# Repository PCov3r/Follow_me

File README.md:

# Follow me

***Follow me*** est un projet de première année d'école d'ingénieur créé par 9 étudiants.<br>
Le but est de suivre une personne grâce à un algorithme de reconnaissance faciale et de faire du streaming. On utilise ainsi une raspberry, une carte STM32 et 2 servo-moteurs (un pour le pan et un pour le tilt).<br> On a également implémenté un contrôle manuel du tracking par le biais d'API coté serveur et d'une autre raspberry et d'une STM32 coté commande.

## Serveur et streaming

[Section relative au serveur flask et au tracking](WebServer/FlaskServer/)

Nous avons utilisé la librairie OpenCV pour faire du tracking et la librairie Flask pour implémenter le serveur web et le streaming.<br>

### Tracking et API

La librairie OpenCV possède de manière native différents trackers, dont les détails peuvent être trouvés [ici](https://learnopencv.com/object-tracking-using-opencv-cpp-python/) et [ici](https://ehsangazar.com/object-tracking-with-opencv-fd18ccdd7369). Dans notre cas, nous utilisons le tracker KCF qui est non seulement précis, mais qui retrouve également la personne si celle-ci sort et rentre dans le champ de la caméra. <br>
Le passage du mode tracking automatique au mode contrôle manuel est assuré par le biais d'[API](https://flask.palletsprojects.com/en/2.0.x/api/) sous forme de requêtes HTTP. Le serveur Flask reçoit ces requêtes, en analyse les arguments, et agit en conséquence.
<br>
### Communication avec la carte STM32

La communication entre la Raspberry Pi et la carte STM32 gérant la caméra et les servo-moteurs se fait via le protocole [UART](https://www.raspberrypi.org/documentation/configuration/uart.md). Des détails sur le protocole mis en place se trouvent dans la section relative au contrôle des servos.
Il est à noter que le contrôle des mouvements est pour le moment très naïf. En effet, on indique simplement à la STM32 dans quelle direction on souhaite orienter la caméra. 
<br>
Nous avons en effet abandonné l'idée d'indiquer précisément à la carte la position relative de l'utilisateur, ceci pour des raisons de simplicité et surtout de temps.
Une source d'amélioration serait ainsi d'implémenter cela et d'agir en conséquence sur la vitesse de déplacement afin de s'assurer de ne jamais perdre l'utilisateur.
<br>
### Liste des packages à installer pour le serveur web et tracking

pip : ``sudo apt-get install python3-pip`` <br>
imutils : ``pip3 install imutils`` <br>
opencv : ``apt-get install python3-opencv``<br>
flask : ``pip3 install flask``

<br>
<br>

## Contrôle des mouvements de la caméra

[Section relative au contrôle des mouvements de la caméra](/servo/)

### Les servomoteurs (Mouvement pan (axe X) et tilt (axe Y))

Afin de contrôler les servomoteurs qui régissent les mouvements de la caméra, nous avons créé une libraire en C pour traduire les instructions en une série de valeurs que les servomoteurs comprennent.<br>
Les moteurs ont une mémoire (une RAM qui s'efface à chaque mise hors tension et une ROM permanente) dans laquelle nous pouvons stocker des valeurs. Chaque case mémoire contient l'état d'un certain paramètre du moteur : une case stocke l'angle du moteur, une autre stocke sa vitesse et une autre stocke sa température interne par exemple. Ainsi, pour faire tourner le moteur, nous n'envoyons pas "tourne à 120°" mais plutôt "écrit 120° dans la case mémoire qui stocke l'angle du moteur".
<p align="center"><a href="https://emanual.robotis.com/docs/en/dxl/ax/ax-12a/#control-table-of-eeprom-area">Les cases mémoires ainsi que leur fonction sont accessibles ici</a></p>
La librairie permet de faire cette traduction pour facilement commander les moteurs. Nous avons codé presque toutes les fonctions présentes sur le site, pour pouvoir réutiliser cette librairie pour d'éventuels futurs projets.<br>
Maintenant que nous savons <i>quoi</i> envoyer, il faut se demander <i>comment</i>. En effet, la communication avec le moteur ne se fait via qu'un seul fil. Le protocole est donc plutôt simple : <br>
- Tant qu'il ne se passe rien, la sortie de la carte reste à l'état haut (5V).<br>
- Si la carte envoie une instruction, alors la sortie va passer à l'état bas (0V), et à partir de là le moteur va commencer à lire la série de 0 et de 1.<br>
- Le moteur interprète la série binaire, exécute l'action correspondante, puis renvoie à la carte une autre série binaire qui peut être une erreur, la valeur de la case mémoire ou bien un code de bon déroulement.<br>
Ce protocole s'appelle l'Half-Uart (en opposition avec l'Uart qui utilise 2 fils : un pour l'envoi et un pour la réception). <a href="https://emanual.robotis.com/docs/en/dxl/protocol1/">Plus de détails sur la communication avec les moteurs ici</a>.

### Le zoom et le focus de la caméra

Le contrôle du zoom et de la caméra fonctionne exactement comme les moteurs, seul le protocole de comunication change, cette fois-ci c'est l'i2c. Les cases mémoires ainsi que les valeurs [sont décrites ici](https://www.arducam.com/docs/cameras-for-raspberry-pi/ptz-camera/software/). On ajoute aussi la [datasheet de la caméra](https://www.arducam.com/downloads/modules/RaspberryPi_camera/OV5647DS.pdf)

### La communication STM/Raspberry

Enfin, c'est la Raspberry qui s'occupe du tracking du visage, c'est donc elle qui envoie les ordres de mouvements de la caméra. Or, les moteurs sont commandés par la carte STM. Il faut donc établir une communication entre les deux. Nous avons donc établi un code entre nous pour échanger ces instructions, via le protocole Uart.

## Commande manuelle

[Section relative à la commande manuelle du tracking](WebServer/clientSide/)

En plus du tracking, nous avons ajouté à l'utilisateur la possibilité de prendre la main sur le contrôle de la caméra via un boitier de commande relié au serveur principal par API.<br>
Ainsi, grâce à un simple interrupteur, on passe du mode automatique au mode manuel et inversement.
Le contrôle des mouvements selon les axes x et y ainsi que du zoom sont assurés par 2 joysticks. <br> <br>
L'acquisition se fait via une carte STM32, qui communique ces informations à une raspberry via la librairie ``pyserial``. Cette dernière envoie ensuite des requêtes HTTP au serveur Flask via la librairie ``pycurl``.
<br>
De plus amples informations peuvent être trouvées dans les commentaires accompagnant chaque code.

### Liste des packages à installer pour le contrôle manuel de la caméra

pip : ``sudo apt-get install python3-pip`` <br>
pyserial : ``pip3 install pyserial`` <br>
pycurl : ``pip3 install pycurl``

<br>
<br>

## Du POE !
[Section relative au shield POE](/POE/)

Notre cahier des charges imposait également la conception d'un shield POE. <br>
L’objectif de notre Shield POE est de recevoir le courant par un câble ethernet branché à la Raspberry Pi 4B afin d’alimenter cette dernière, mais aussi les moteurs permettant d'orienter la caméra. <br>

**Versioning:** <br>
<br>
* V1 <br>
 La tension fournie par le distributeur POE au travers du câble Ethernet est une tension continue comprise entre 42V et 52V, il nous a donc fallu utiliser deux abaisseurs de tensions afin d’obtenir les tensions de 5V et 11.1V nécessaires respectivement pour l’alimentation de la Raspberry Pi 4B et des moteurs. <br>
La première tension souhaitée est créée à partir de l’abaisseur LM2576HVS (utilisé dans la configuration présentée à la page 19 de la [DataSheet](POE/DataSheet_LM2576HVS.pdf) avec lesvaleurs de composants calculés grâce aux instructions et tables données page 19,20,21). Le montage entourant l’abaisseur 11.1V  LM46002-Q1 est également tiré de sa propre [Datasheet](POE/DataSheet_LM46002-Q1.pdf) page 24. <br>
Les valeurs des composants de ces deux montages retenus apparaissent dans le Schematics du projet EAGLE.

* V2 <br>
 La première version avait pour seul objectif de vérifier que les montages sélectionnés permettaient en effet d’obtenir les tensions désirées. Une fois cela validé, nous avons créé cette deuxième version, comportant les mêmes circuits, mais sur un PCB adapté à la Raspberry Pi 4B. Le shield se fixe directement sur les 4 pins de la Raspberry Pi 4B destinées à la redistribution de l'énergie reçue par le cable ethernet, et sur les pins 2 et 4 (5v), 6 et 9 (GND) pour l’alimentation directe de la Raspberry. Il se fixe également sur les pins 8 et 10 relatives à l'UART afin de communiquer avec les moteurs.
 
 Fonctions | Pins correspondantes
------------ | -------------
Récupérer et redistribuer l'énergie reçue par Ethernet | Pins près du jack Ethernet (POE hat)
Alimenter la Raspberry | 2, 4 (5v) <br> 6, 9 (GND)
Etablir la liaison UART STM/RPi | 8, 10

* V3 <br>
 Nous avons compris lors de la réalisation de la deuxième version du PCB que l’attribution des pins destinées au POE sur la Raspberry dépendent du câble ethernet et de l’injecteur POE utilisés. Afin que notre shield puisse fonctionner correctement avec tous les câbles ethernet et tous les injecteurs POE, nous avons rajouté sur cette version finale un pont de diodes, qui, peu importe l’attribution des pins de la Raspberry Pi 4B, nous garantit une tension positive et une masse.

**DISCLAIMER:** <br>
La norme POE+ nécessiterait un composant supplémentaire (non implémenté ici) sur le shield pour être utilisable. Ce shield POE n’est donc absolument pas compatible avec la norme POE+, et ne fonctionnera pas si cette norme est sélectionnée dans les paramètres de l’injecteur. (Si vous sélectionnez la norme POE+ avec ce shield POE, l’injecteur délivrera une tension intermittente bien en dessous de la valeur attendue, et sera donc inutilisable.)  Be advised. <br>
La capacité Cin doit selon la datasheet supporter une tension de 100V. Cette dernière est difficile à trouver mais peut être achetée ici: https://fr.farnell.com/tdk/ckg57nx7r2a106m500jh/condensateur-10uf-100v-mlcc-2220/dp/1886985

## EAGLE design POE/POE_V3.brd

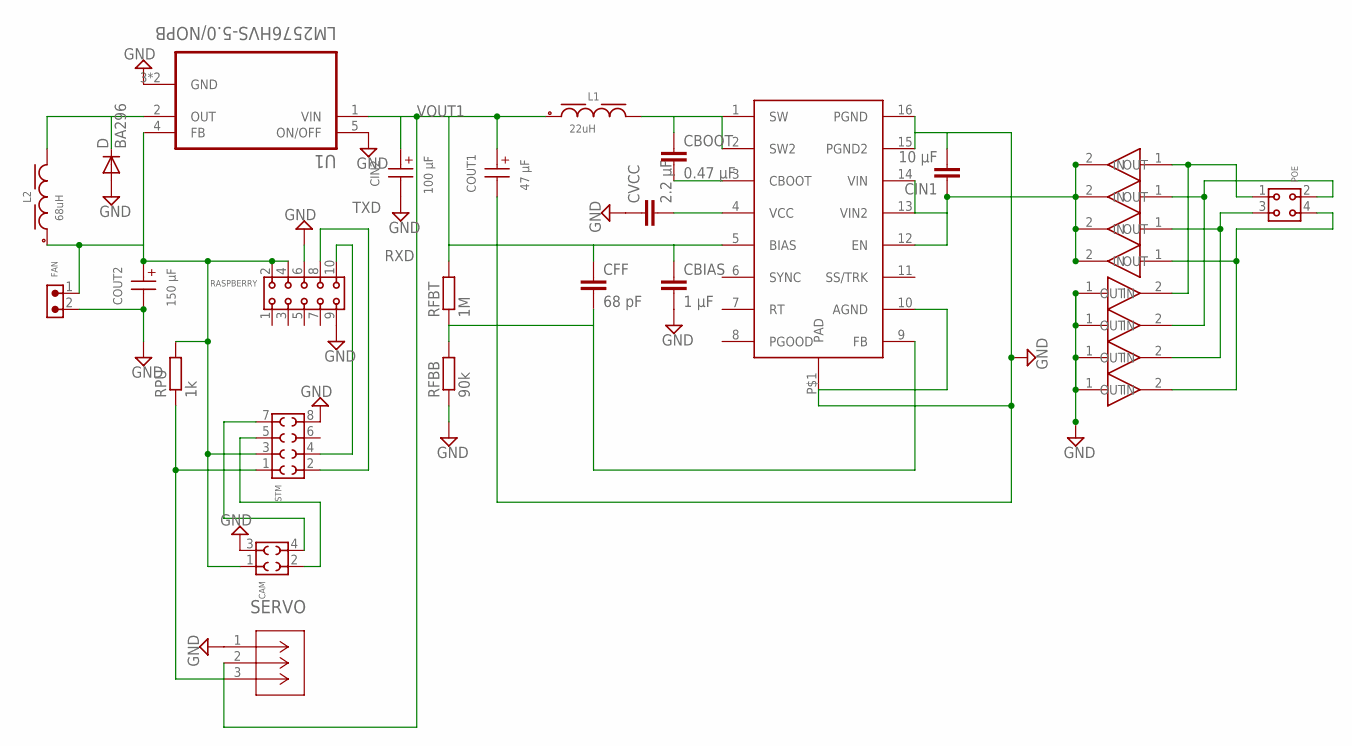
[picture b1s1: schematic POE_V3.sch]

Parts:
CAM: 6100XX21821_61000421821; 61000421821
CBIAS: 1 µF; C1206
CBOOT: 0.47 µF; C1206
CFF: 68 pF; C1206
CIN1: 10 µF; C2220K
CIN2: 100 µF; WCAP-ASLI_6.3X5.5(DXL)
COUT1: 47 µF; WCAP-ASLI_5X5.5(DXL)
COUT2: 150 µF; WCAP-ASLI_6.3X5.5(DXL)
CVCC: 2.2 µF; C1206
D: BA296; P2-15
FAN: 6130XX11021_61300211021; 61300211021
L1: 22uH; WE-PD_1260
L2: 68uH; WE-PD_1210
POE: 6130XX21821_61300421821; 61300421821
RASPBERRY: 6130XX21821_61301021821; 61301021821
RFBB: 90k; M1206
RFBT: 1M; M1206
RPU: 1k; M1206
SERVO: 22035035; CON_22035035
STM: 6100XX21821_61000821821; 61000821821
U1: LM2576HVS-5.0/NOPB; VREG_TPS79625KTTR
U$1: LM46002; TSSOP16
U$2, U$3, U$4, U$5, U$6, U$7, U$8, U$9: RGF1D

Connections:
GND: CAM.3, CBIAS.2, CIN1.2, CIN2.2 (-), COUT1.2 (-), COUT2.2 (-), CVCC.1, D.A, FAN.2, RASPBERRY.6, RASPBERRY.9, RFBB.1, SERVO.1, STM.8, U1.3 (GND), U1.5 (ON/OFF), U1.6 (GND), U$1.10 (AGND), U$1.15 (PGND2), U$1.16 (PGND), U$1.P$1 (PAD), U$4.1 (IN), U$5.1 (IN), U$8.1 (IN), U$9.1 (IN)
unnamed: CBOOT.1, L1.2, U$1.1 (SW), U$1.2 (SW2)
unnamed: CBOOT.2, U$1.3 (CBOOT)
unnamed: CVCC.2, U$1.4 (VCC)
unnamed: POE.1, U$2.1 (IN), U$4.2 (OUT)
unnamed: POE.2, U$3.1 (IN), U$5.2 (OUT)
unnamed: D.C, L2.2, U1.2 (OUT)
unnamed: CAM.4, STM.7
unnamed: CAM.2, STM.5
unnamed: RPU.1, SERVO.3, STM.1
unnamed: POE.3, U$6.1 (IN), U$8.2 (OUT)
unnamed: POE.4, U$7.1 (IN), U$9.2 (OUT)
RFBT: CFF.2, RFBB.2, RFBT.1, U$1.9 (FB)
RXD: RASPBERRY.10, STM.4
TXD: RASPBERRY.8, STM.2
VIN: CIN1.1, U$1.12 (EN), U$1.13 (VIN2), U$1.14 (VIN), U$2.2 (OUT), U$3.2 (OUT), U$6.2 (OUT), U$7.2 (OUT)
VOUT1: CBIAS.1, CFF.1, CIN2.1 (+), COUT1.1 (+), L1.1, RFBT.2, SERVO.2, U1.1 (VIN), U$1.5 (BIAS)
VOUT2: CAM.1, COUT2.1 (+), FAN.1, L2.1, RASPBERRY.2, RASPBERRY.4, RPU.2, STM.3, U1.4 (FB)

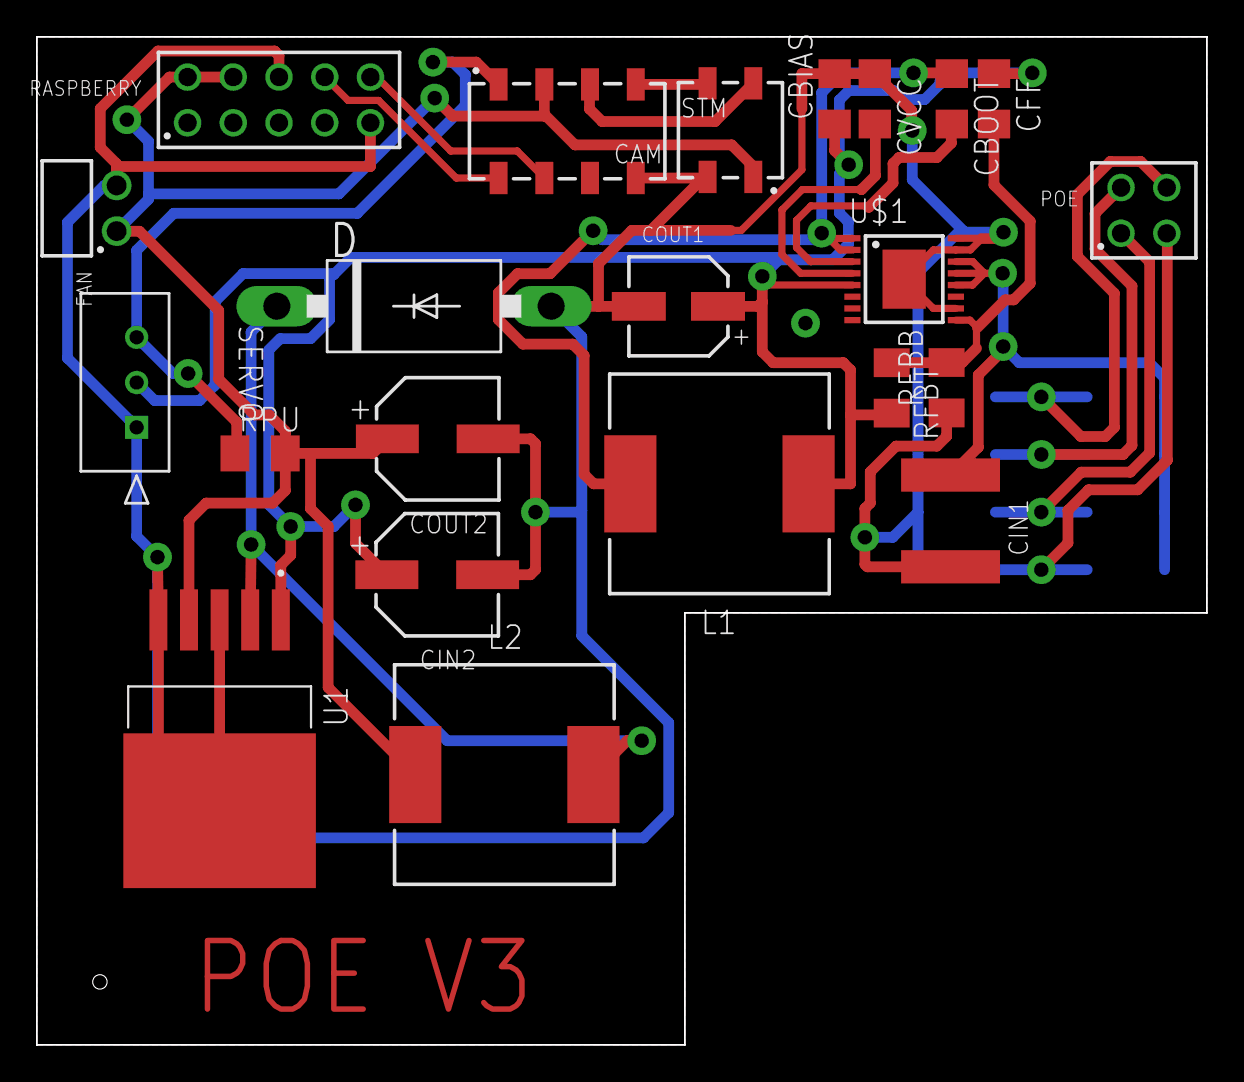
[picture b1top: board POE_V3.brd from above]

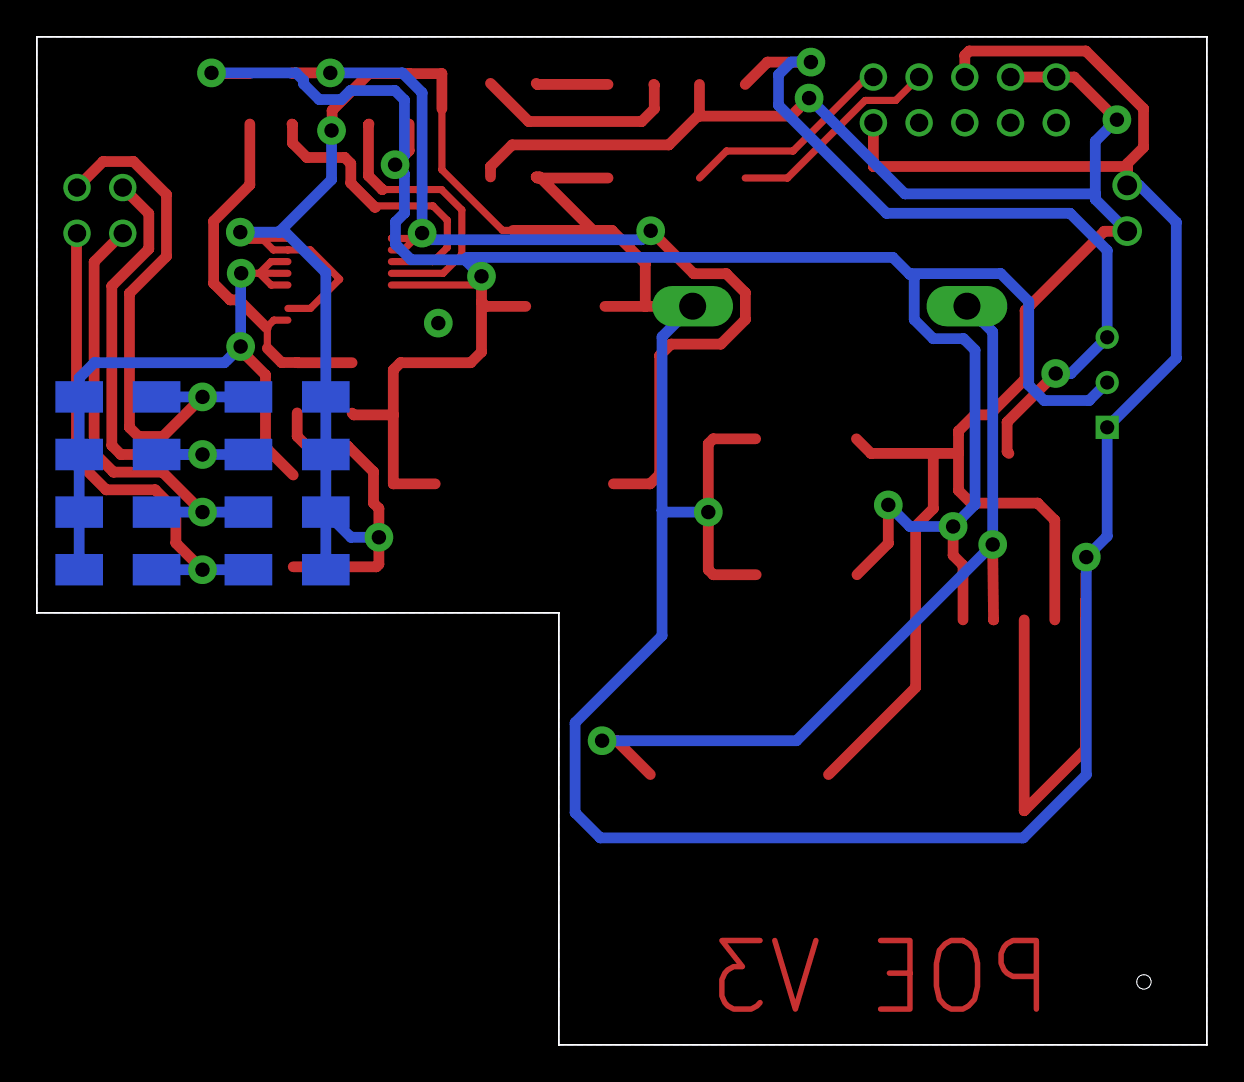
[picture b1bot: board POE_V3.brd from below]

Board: 2 copper layers, 65.0 x 56.0 mm, 30 parts (8 on the bottom side), 18 nets.

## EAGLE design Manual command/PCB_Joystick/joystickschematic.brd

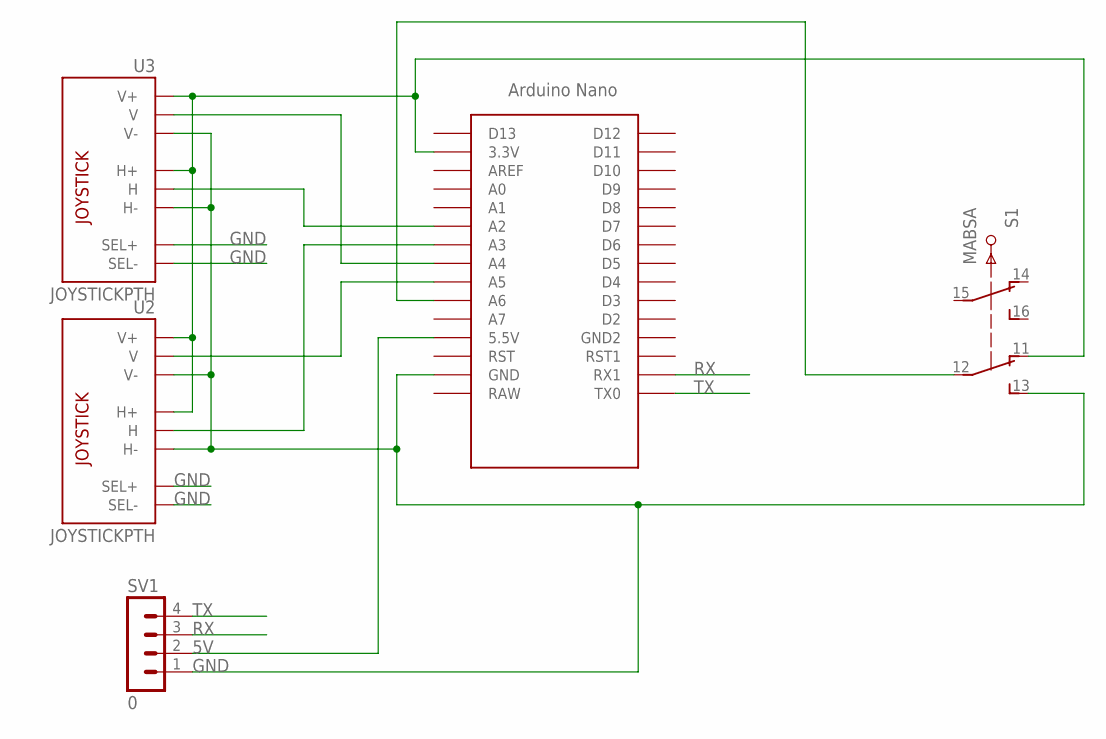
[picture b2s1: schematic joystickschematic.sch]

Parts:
S1: MABSA
SV1: 0; MA04-1
U2, U3: JOYSTICKPTH; JOYSTICK
U$2: NANO

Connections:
3.3V: S1.11, U2.H1 (H+), U2.V1 (V+), U3.H1 (H+), U3.V1 (V+), U$2.3.3V
5V: SV1.2, U$2.5V (5.5V)
GND: S1.13, SV1.1, U2.B1A (SEL+), U2.B2A (SEL-), U2.H3 (H-), U2.V3 (V-), U3.B1A (SEL+), U3.B2A (SEL-), U3.H3 (H-), U3.V3 (V-), U$2.GND
unnamed: U3.V2 (V), U$2.A4
unnamed: U3.H2 (H), U$2.A2
unnamed: U2.H2 (H), U$2.A3
unnamed: U2.V2 (V), U$2.A5
unnamed: S1.12, U$2.A6
RX: SV1.3, U$2.RX1
TX: SV1.4, U$2.TX0

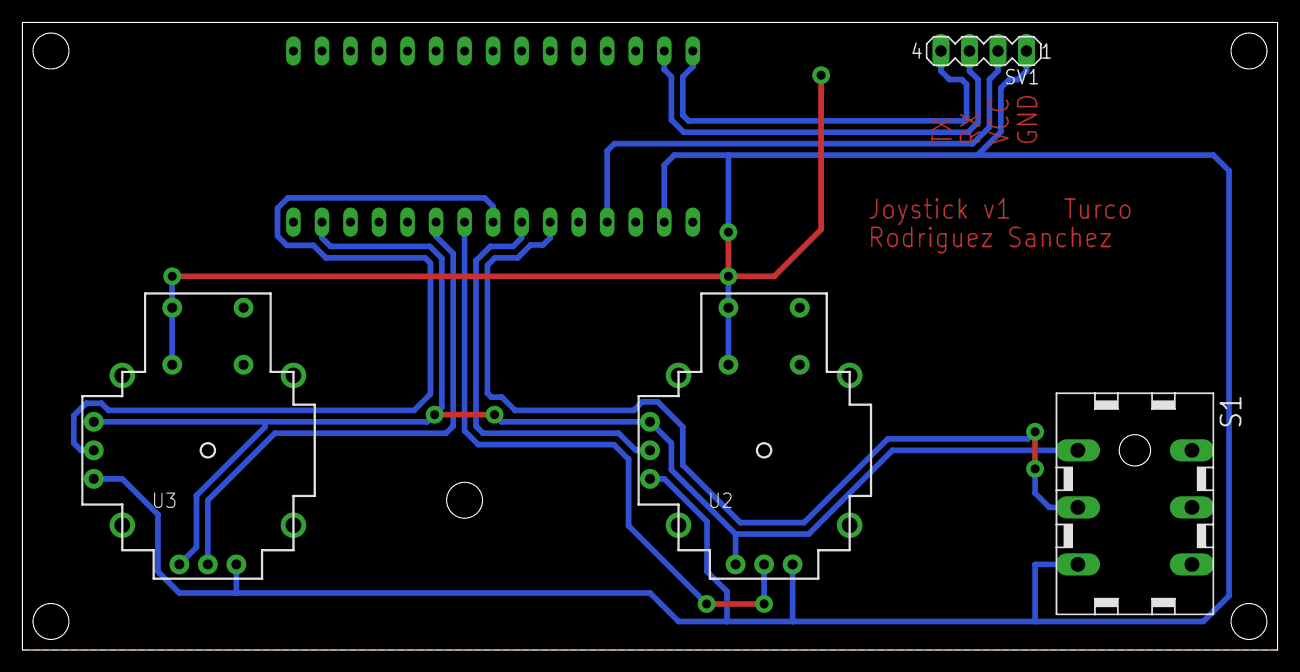
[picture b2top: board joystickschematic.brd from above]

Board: 2 copper layers, 111.8 x 55.9 mm, 5 parts (0 on the bottom side), 10 nets.

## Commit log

2021-04-08 Rename video.pi to video.py
2021-04-20 Create Tracker_position.py
    Ce script inclut en plus de l'autocorrection le calcul de la position de la personne par rapport à la caméra.
2021-05-09 Create serverSide
2021-05-09 Rename WebServer/serverSide/main.py to WebServer/FlaskServer/main.py
2021-05-09 Rename WebServer/video.py to WebServer/FlaskServer/video.py
2021-05-09 Rename WebServer/index.html to WebServer/FlaskServer/index.html
2021-05-09 Rename WebServer/app.py to WebServer/Deprecated/app.py
2021-05-09 Rename WebServer/main.py to WebServer/Deprecated/main.py
2021-05-16 Create ytStream.py
    created script for yt live streaming
2021-06-03 Create main_03_06_2021
2021-06-12 Updated index.html path
2021-06-12 Added comments on the script
2021-06-12 Created UART communication library
2021-06-12 Rename Tracker_position_V1.py to Tracker_position_V2.py
2021-06-12 Rename WebServer/Flasfocus_lib.py to WebServer/FlaskServer/focus_lib.py
2021-06-12 Update main_03_06_2021
2021-06-12 Create install.sh
    Created the bash script to install all dependencies
2021-06-12 Add files via upload
    Added file for tracking
2021-06-13 Rename mainSTM.c to main.c
2021-06-13 Added 3D models
2021-08-04 Fixed indent problem
2021-08-17 Updated script to python3

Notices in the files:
parts and their libraries:
Eagle_WR-PHD: Copyright: Würth Elektronik
COPYRIGHT: Copyright (C) 2018 Accelerated Designs. All rights reserved
